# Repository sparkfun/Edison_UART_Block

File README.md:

SparkFun Edison UART Block
===========================

[*SparkFun Edison UART Block(DEV-13040)*](https://www.sparkfun.com/products/13040)

The Console Basic expansion board delivers power to the Intel Edison while providing a simple console interface via a user's FTDI cable. This is the most minimal solution to get started using the Intel Edison. The Console Basic board can supply 4V and up to 500mA of current to power the Edison and any other expansion boards you may add to your stack. This power is passed through the VSYS line of the Edison.  This is a great board for low power applications that won't require constant console access.  By removing the FTDI USB-UART from the board, current consumption is minimal.  When the FTDI cable is not inserted, it will be necessary to provide external power to the board.

Repository Contents
------------------
* **/Hardware** - All Eagle design files (.brd, .sch)
* **/Production** -Test bed files and production panel files

License Information
------------------
The hardware is released under [Creative Commons ShareAlike 4.0 International](https://creativecommons.org/licenses/by-sa/4.0/).
The code is beerware; if you see me (or any other SparkFun employee) at the local, and you've found our code helpful, please buy us a round!

Distributed as-is; no warranty is given.

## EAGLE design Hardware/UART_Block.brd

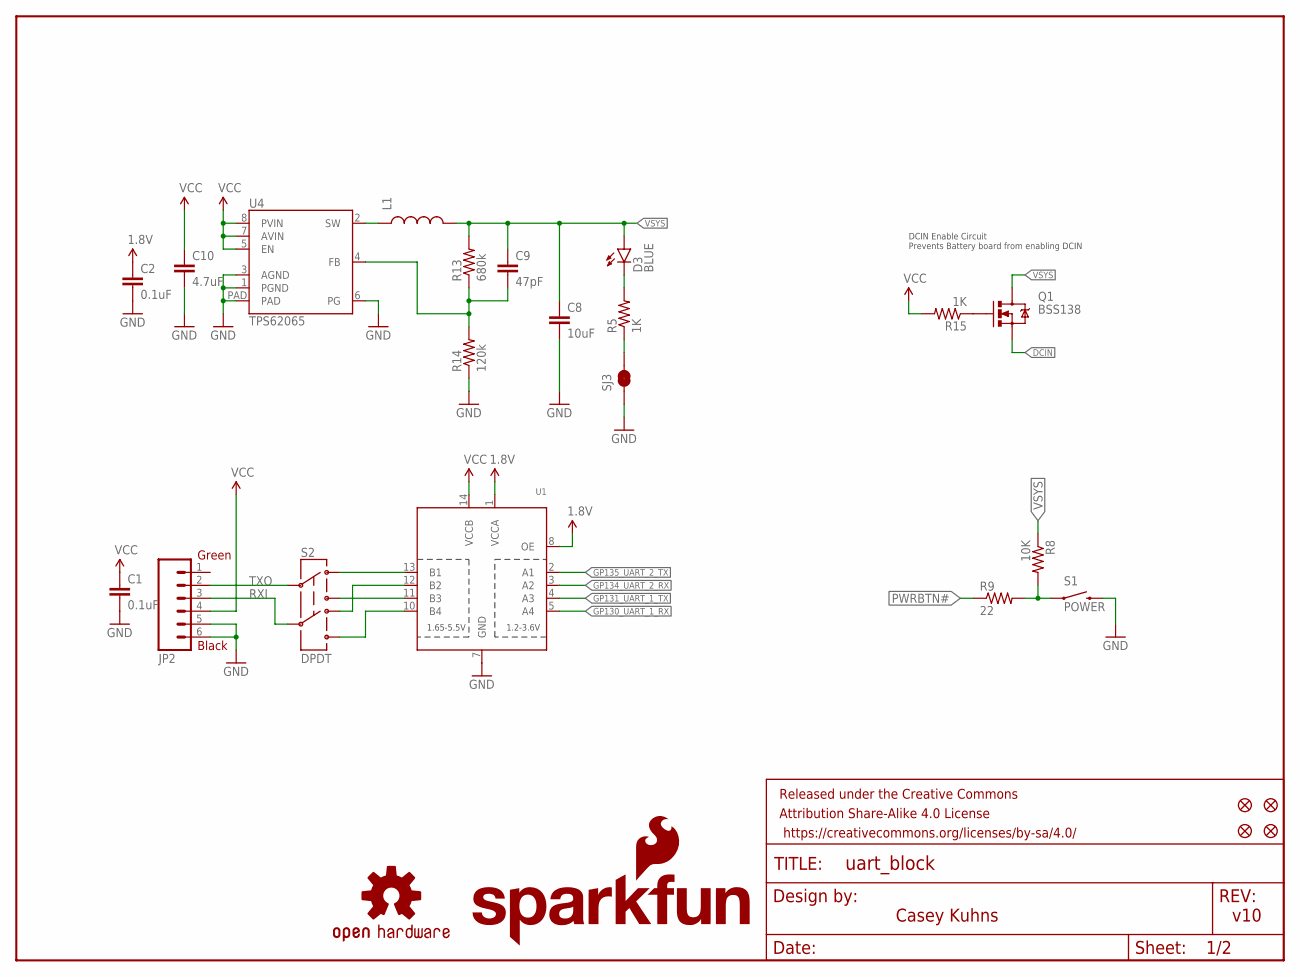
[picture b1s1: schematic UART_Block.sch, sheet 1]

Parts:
C1, C2: 0.1uF; 0603-CAP
C8: 10uF; 1206
C9: 47pF; 0603-CAP
C10: 4.7uF; 0603-CAP
D3: BLUE; LED-0603
FID1, FID2, FID3, FID4: FIDUCIAL1X2; FIDUCIAL-1X2
FRAME1: FRAME-LETTER; CREATIVE_COMMONS
JP2: M06SMD; 1X06-SMD
L1: INDUCTOR; INDUCTOR-SRP4020
LOGO1: SFE_LOGO_NAME_FLAME.1_INCH; SFE_LOGO_NAME_FLAME_.1
LOGO4: OSHW-LOGOS; OSHW-LOGO-S
Q1: BSS138; SOT23-3
R5, R15: 1K; 0603-RES
R8: 10K; 0603-RES
R9: 22; 0603-RES
R13: 680k; 0603-RES
R14: 120k; 0603-RES
S1: POWER; TACTILE_SWITCH-SMD-RIGHT-ANGLE
S2: DPDT; AYZ0202
SJ3: JUMPER-PAD-2-NC_BY_TRACE; PAD-JUMPER-2-NC_BY_TRACE_YES_SILK
U1: TXB0104PWRSOIC14; SO14
U4: TPS62065; WSON-8-PAD

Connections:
1.8V: C2.1, U1.1 (VCCA), U1.8 (OE); also elsewhere on the board
DCIN: Q1.2 (S); also elsewhere on the board
GND: C1.2, C2.2, C8.2, C10.2, JP2.5, JP2.6, R14.1, S1.2, SJ3.1, U1.7 (GND), U4.1 (PGND), U4.3 (AGND), U4.6 (PG), U4.PAD; also elsewhere on the board
GP130_UART_1_RX: U1.5 (A4); also elsewhere on the board
GP131_UART_1_TX: U1.4 (A3); also elsewhere on the board
GP134_UART_2_RX: U1.3 (A2); also elsewhere on the board
GP135_UART_2_TX: U1.2 (A1); also elsewhere on the board
unnamed: Q1.1 (G), R15.1
unnamed: D3.C, R5.2
unnamed: R5.1, SJ3.2
unnamed: R8.2, R9.2, S1.1
unnamed: C9.2, R13.1, R14.2, U4.4 (FB)
unnamed: L1.P$1 (1), U4.2 (SW)
PWRBTN#: R9.1; also elsewhere on the board
RXI: JP2.3, S2.5
TXO: JP2.2, S2.2
UART1RX: S2.6, U1.10 (B4)
UART1TX: S2.3, U1.11 (B3)
UART2RX: S2.4, U1.12 (B2)
UART2TX: S2.1, U1.13 (B1)
VCC: C1.1, C10.1, JP2.4, R15.2, U1.14 (VCCB), U4.5 (EN), U4.7 (AVIN), U4.8 (PVIN)
VSYS: C8.1, C9.1, D3.A, L1.P$2 (2), Q1.3 (D), R8.1, R13.2; also elsewhere on the board

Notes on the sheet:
Black
Green
v10
Casey Kuhns
DCIN Enable Circuit Prevents Battery board from enabling DCIN

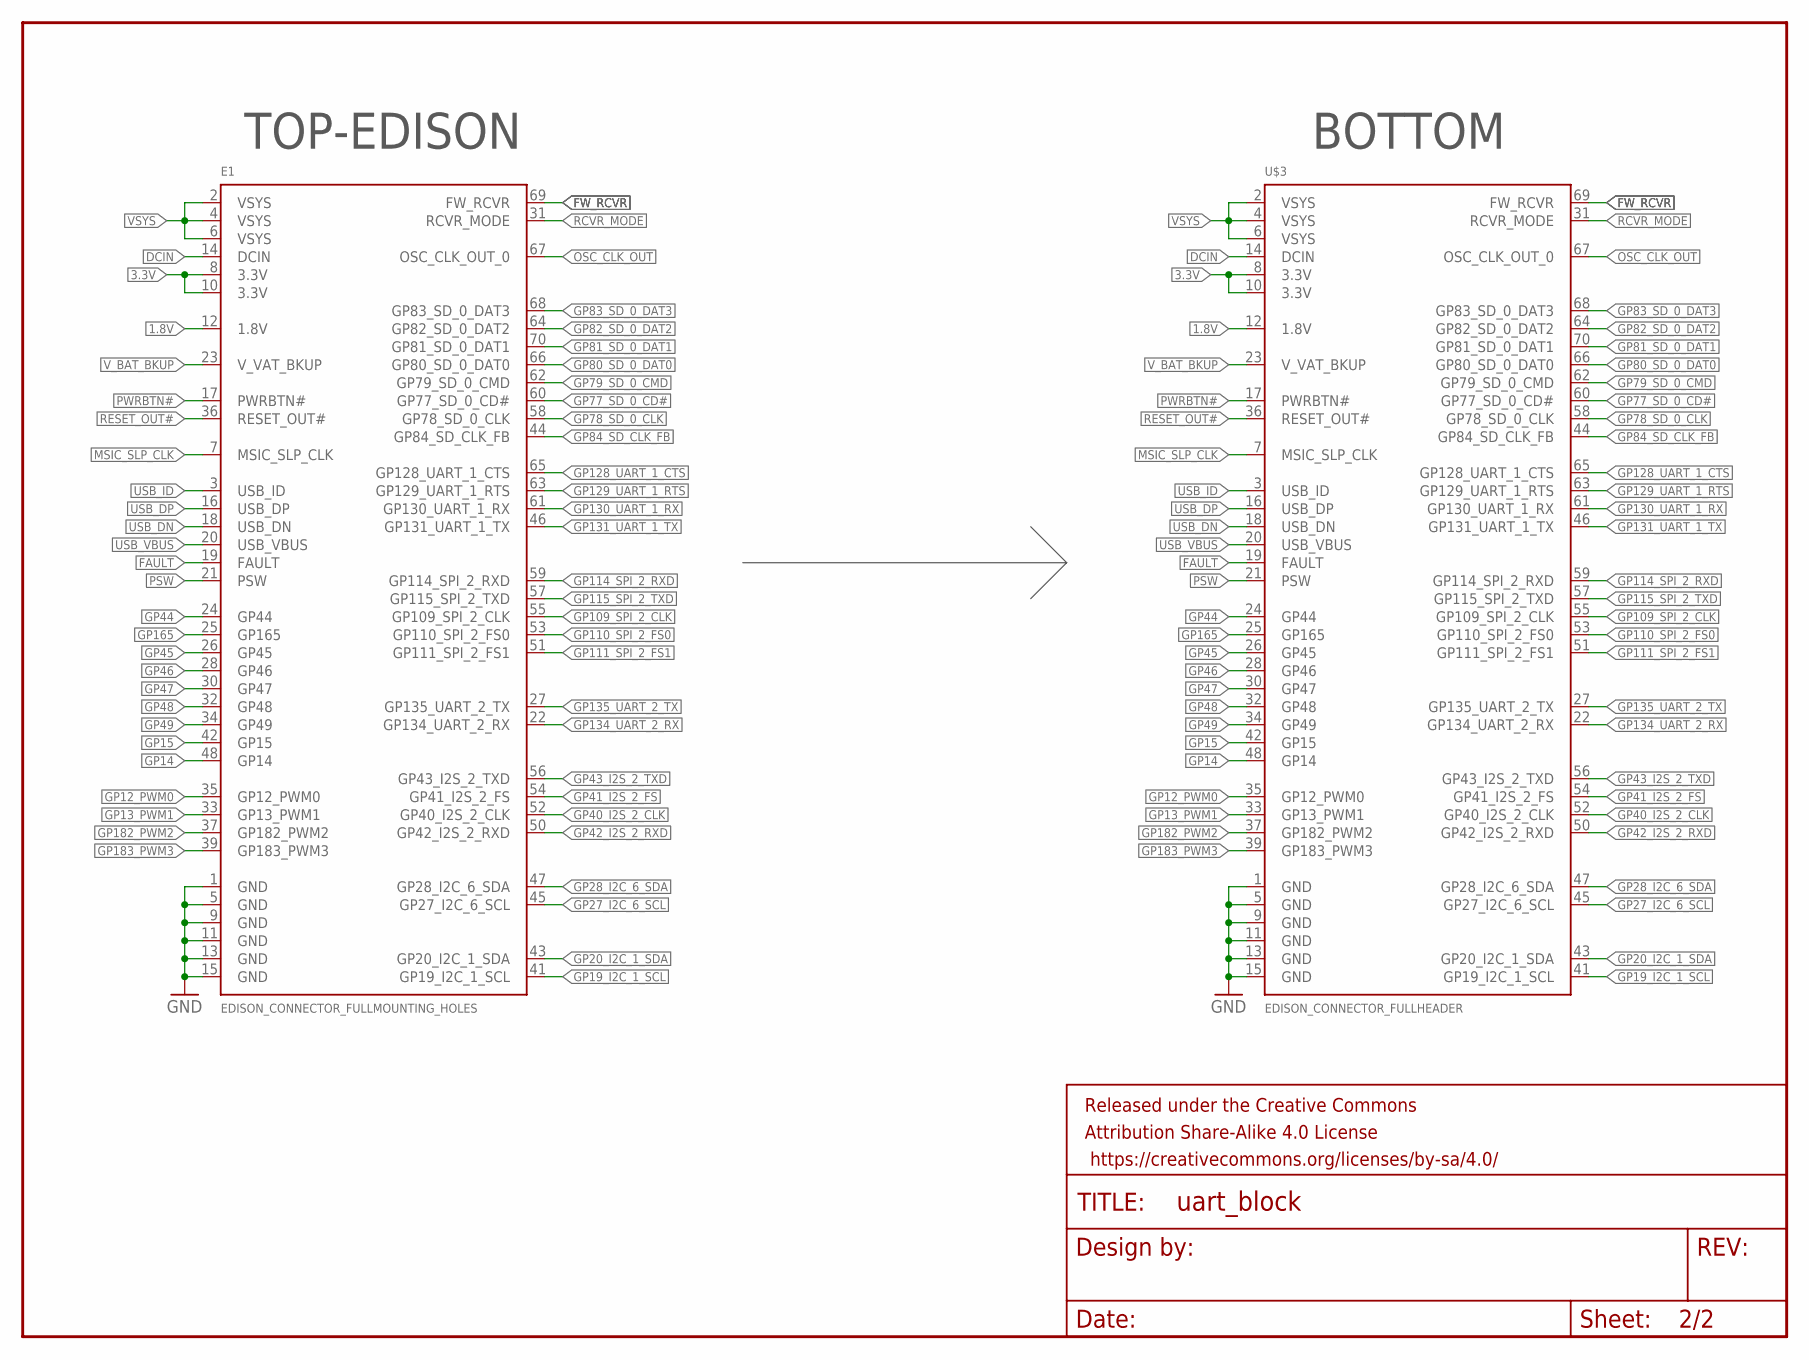
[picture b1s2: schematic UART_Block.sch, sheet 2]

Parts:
E1: EDISON_CONNECTOR_FULLMOUNTING_HOLES; EDISON_DAUGHTER
FRAME2: FRAME-LETTER; CREATIVE_COMMONS
U$3: EDISON_CONNECTOR_FULLHEADER; DF40C-70DP-0.4(51)

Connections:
1.8V: E1.12 (1.8V), U$3.12 (1.8V); also elsewhere on the board
3.3V: E1.8 (3.3V), E1.10 (3.3V), U$3.8 (3.3V), U$3.10 (3.3V)
DCIN: E1.14 (DCIN), U$3.14 (DCIN); also elsewhere on the board
FAULT: E1.19 (FAULT), U$3.19 (FAULT)
FW_RCVR: E1.69 (FW_RCVR), U$3.69 (FW_RCVR)
GND: E1.1 (GND), E1.5 (GND), E1.9 (GND), E1.11 (GND), E1.13 (GND), E1.15 (GND), U$3.1 (GND), U$3.5 (GND), U$3.9 (GND), U$3.11 (GND), U$3.13 (GND), U$3.15 (GND); also elsewhere on the board
GP12_PWM0: E1.35 (GP12_PWM0), U$3.35 (GP12_PWM0)
GP13_PWM1: E1.33 (GP13_PWM1), U$3.33 (GP13_PWM1)
GP14: E1.48 (GP14), U$3.48 (GP14)
GP15: E1.42 (GP15), U$3.42 (GP15)
GP19_I2C_1_SCL: E1.41 (GP19_I2C_1_SCL), U$3.41 (GP19_I2C_1_SCL)
GP20_I2C_1_SDA: E1.43 (GP20_I2C_1_SDA), U$3.43 (GP20_I2C_1_SDA)
GP27_I2C_6_SCL: E1.45 (GP27_I2C_6_SCL), U$3.45 (GP27_I2C_6_SCL)
GP28_I2C_6_SDA: E1.47 (GP28_I2C_6_SDA), U$3.47 (GP28_I2C_6_SDA)
GP40_I2S_2_CLK: E1.52 (GP40_I2S_2_CLK), U$3.52 (GP40_I2S_2_CLK)
GP41_I2S_2_FS: E1.54 (GP41_I2S_2_FS), U$3.54 (GP41_I2S_2_FS)
GP42_I2S_2_RXD: E1.50 (GP42_I2S_2_RXD), U$3.50 (GP42_I2S_2_RXD)
GP43_I2S_2_TXD: E1.56 (GP43_I2S_2_TXD), U$3.56 (GP43_I2S_2_TXD)
GP44: E1.24 (GP44), U$3.24 (GP44)
GP45: E1.26 (GP45), U$3.26 (GP45)
GP46: E1.28 (GP46), U$3.28 (GP46)
GP47: E1.30 (GP47), U$3.30 (GP47)
GP48: E1.32 (GP48), U$3.32 (GP48)
GP49: E1.34 (GP49), U$3.34 (GP49)
GP77_SD_0_CD#: E1.60 (GP77_SD_0_CD#), U$3.60 (GP77_SD_0_CD#)
GP78_SD_0_CLK: E1.58 (GP78_SD_0_CLK), U$3.58 (GP78_SD_0_CLK)
GP79_SD_0_CMD: E1.62 (GP79_SD_0_CMD), U$3.62 (GP79_SD_0_CMD)
GP80_SD_0_DAT0: E1.66 (GP80_SD_0_DAT0), U$3.66 (GP80_SD_0_DAT0)
GP81_SD_0_DAT1: E1.70 (GP81_SD_0_DAT1), U$3.70 (GP81_SD_0_DAT1)
GP82_SD_0_DAT2: E1.64 (GP82_SD_0_DAT2), U$3.64 (GP82_SD_0_DAT2)
GP83_SD_0_DAT3: E1.68 (GP83_SD_0_DAT3), U$3.68 (GP83_SD_0_DAT3)
GP84_SD_CLK_FB: E1.44 (GP84_SD_CLK_FB), U$3.44 (GP84_SD_CLK_FB)
GP109_SPI_2_CLK: E1.55 (GP109_SPI_2_CLK), U$3.55 (GP109_SPI_2_CLK)
GP110_SPI_2_FS0: E1.53 (GP110_SPI_2_FS0), U$3.53 (GP110_SPI_2_FS0)
GP111_SPI_2_FS1: E1.51 (GP111_SPI_2_FS1), U$3.51 (GP111_SPI_2_FS1)
GP114_SPI_2_RXD: E1.59 (GP114_SPI_2_RXD), U$3.59 (GP114_SPI_2_RXD)
GP115_SPI_2_TXD: E1.57 (GP115_SPI_2_TXD), U$3.57 (GP115_SPI_2_TXD)
GP128_UART_1_CTS: E1.65 (GP128_UART_1_CTS), U$3.65 (GP128_UART_1_CTS)
GP129_UART_1_RTS: E1.63 (GP129_UART_1_RTS), U$3.63 (GP129_UART_1_RTS)
GP130_UART_1_RX: E1.61 (GP130_UART_1_RX), U$3.61 (GP130_UART_1_RX); also elsewhere on the board
GP131_UART_1_TX: E1.46 (GP131_UART_1_TX), U$3.46 (GP131_UART_1_TX); also elsewhere on the board
GP134_UART_2_RX: E1.22 (GP134_UART_2_RX), U$3.22 (GP134_UART_2_RX); also elsewhere on the board
GP135_UART_2_TX: E1.27 (GP135_UART_2_TX), U$3.27 (GP135_UART_2_TX); also elsewhere on the board
GP165: E1.25 (GP165), U$3.25 (GP165)
GP182_PWM2: E1.37 (GP182_PWM2), U$3.37 (GP182_PWM2)
GP183_PWM3: E1.39 (GP183_PWM3), U$3.39 (GP183_PWM3)
MSIC_SLP_CLK: E1.7 (MSIC_SLP_CLK), U$3.7 (MSIC_SLP_CLK)
OSC_CLK_OUT: E1.67 (OSC_CLK_OUT_0), U$3.67 (OSC_CLK_OUT_0)
PSW: E1.21 (PSW), U$3.21 (PSW)
PWRBTN#: E1.17 (PWRBTN#), U$3.17 (PWRBTN#); also elsewhere on the board
RCVR_MODE: E1.31 (RCVR_MODE), U$3.31 (RCVR_MODE)
RESET_OUT#: E1.36 (RESET_OUT#), U$3.36 (RESET_OUT#)
USB_DN: E1.18 (USB_DN), U$3.18 (USB_DN)
USB_DP: E1.16 (USB_DP), U$3.16 (USB_DP)
USB_ID: E1.3 (USB_ID), U$3.3 (USB_ID)
USB_VBUS: E1.20 (USB_VBUS), U$3.20 (USB_VBUS)
VSYS: E1.2 (VSYS), E1.4 (VSYS), E1.6 (VSYS), U$3.2 (VSYS), U$3.4 (VSYS), U$3.6 (VSYS); also elsewhere on the board
V_BAT_BKUP: E1.23 (V_VAT_BKUP), U$3.23 (V_VAT_BKUP)

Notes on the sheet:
TOP-EDISON
BOTTOM

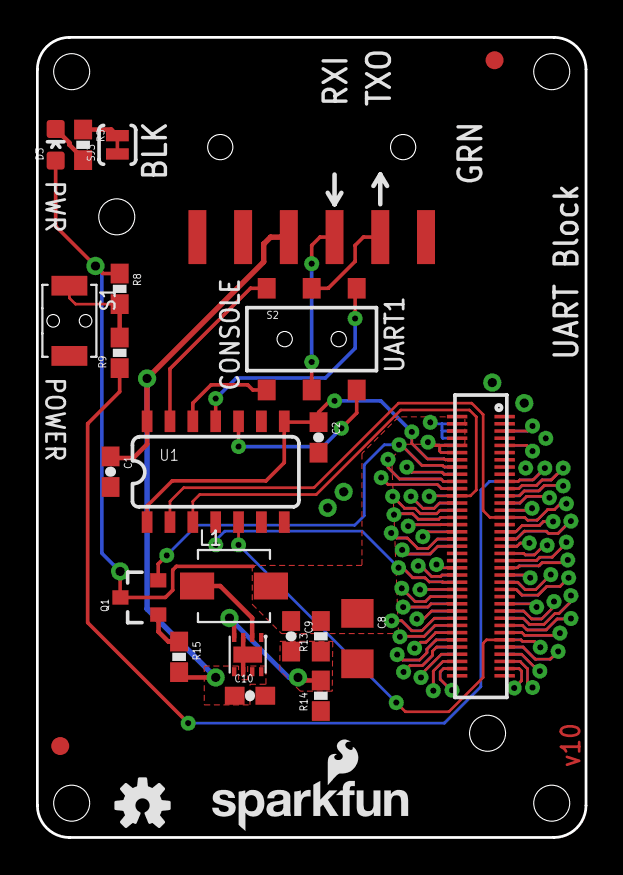
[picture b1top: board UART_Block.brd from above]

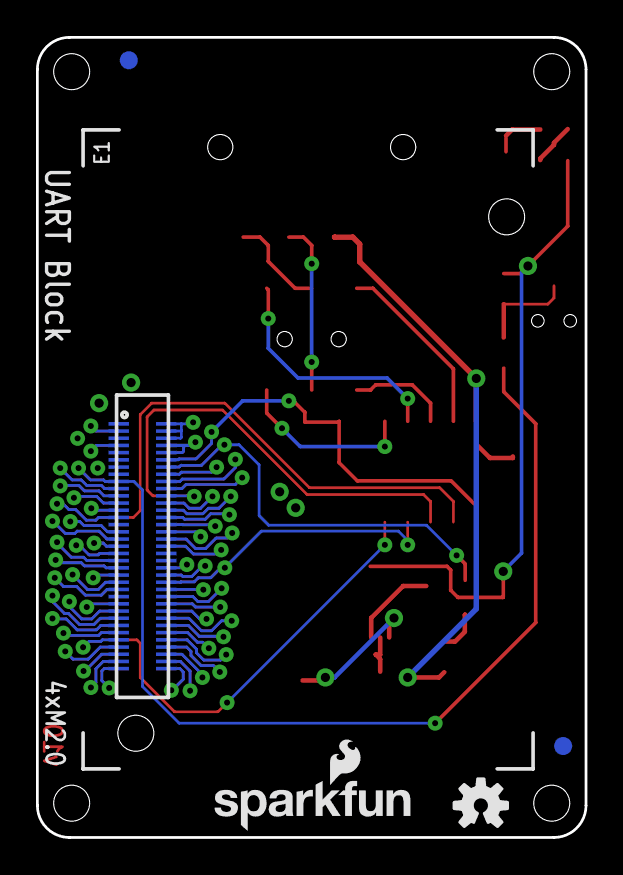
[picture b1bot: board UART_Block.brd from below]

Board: 2 copper layers, 30.5 x 44.5 mm, 32 parts (6 on the bottom side), 71 nets.

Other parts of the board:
LOGO2: OSHW-LOGOS; OSHW-LOGO-S
LOGO3: SFE_LOGO_NAME_FLAME.1_INCH; SFE_LOGO_NAME_FLAME_.1

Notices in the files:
parts and their libraries:
SparkFun-Aesthetics: Licensing: Creative Commons ShareAlike 4.0 International - https://creativecommons.org/licenses/by-sa/4.0
SparkFun-Aesthetics: Released under the Creative Commons Attribution Share-Alike 4.0 License
SparkFun-Aesthetics: Released under the Creative Commons
